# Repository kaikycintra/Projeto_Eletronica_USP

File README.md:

# SSC0180 - Eletrônica para Computação

Repositório para os trabalhos desenvolvidos na disciplina SSC0180 - Eletrônica para Computação, ministrada pelo professor Eduardo do Valle Simoes da USP

Membros dos projetos:

- Antônio Carlos de Almeida Micheli Neto - 14559013
- Maria Rita Gomides Cruz Hott - 14758717
- Kaiky Henrique Ribeiro Cintra - 13731160
- Luiz Fellipe Catuzzi Araujo Hotoshi - 11871198
- Julia Cavallio Orlando - 14758721

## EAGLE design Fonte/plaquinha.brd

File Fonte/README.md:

# Fonte
Nesse projeto, montamos uma fonte de tensão ajustável de 3V a 12V com capacidade de 100mA partindo de uma corrente alternada de 127V e 60Hz.

&nbsp;

Nós e a fonte <3

## Vídeos
Fonte construída: https://youtu.be/3VAhmxHJs3s

Functionamento do circuito: https://youtu.be/wee167FJJZs

## Componentes do Circuito

| Componente | Preço |
| --- | --- |
| Capacitor 1mF x2 | R$0,50 * 2 = R$1,00 |
| LED x2 | R$0,50 * 2 = R$1,00 |
| Diodo Zener 13V x2 | R$0,62 * 2 = R$1,24 |
| Transistor NPN 60V | R$1,60 |
| Potenciômetro Linear 10kΩ | R$7,00 |
| Resistor 3k3Ω x10 | R$0,07 * 10 = R$0,70 |
| Resistor 4k7Ω x10 | R$0,07 * 10 = R$0,70 |
| Fusível 1,5A | R$1,10 |
| Protoboard BB-01 | R$20,40 |
| Jumper macho-macho 20cm x10 | R$0,70 * 10 = R$7,00 |
| Plug AC 10A | R$6,00 |
| ***TOTAL*** | ***R$47,74*** |

No circuito real nós utilizamos um capacitor de 560μF porque nos venderam o modelo errado. O circuito funcionou como previsto.
Também realizamos a troca de um dos resistores para uma resistência menor já que as conexões reais estavam apresentando valores diferentes.
*Componentes comprados na Ca&Ma em São Carlos, 21/06/2023

### Transformador: 
Dispositivo elétrico que consegue alterar a tensão elétrica de entrada para níveis mais apropriados para uma aplicação específica, fazendo uso de enrolamentos e princípios eletromagnéticos da Lei de Faraday-Lenz. Neste projeto, utilizamos um transformador do laboratório que pôde ajustar a tensão em uma razão de 7.3 entre saída e entrada.
### Diodos:
Componentes elétricos que permitem o fluxo de corrente elétrica em uma única direção. No projeto, são utilizados para montar uma ponte de diodos, que atua como um retificador de tensão, aproveitando ambos os ciclos da corrente alternada.
### Resistores:
Componentes com resistência fixa que garantem o ajuste da corrente elétrica no circuito, permitindo não queimar nada outras partes essenciais.
### Capacitor:
Dispositivo elétrico que consegue armazenar pequenas quantidades de carga elétrica, fornecendo corrente contínua se a tensão interna for maior que a externa. Para conseguir uma flutuação (ripple) menor que 10%, seria necessário um capacitor de no mínimo 790μF (conforme mostrado na seção de cálculos abaixo). No entanto, utilizamos um de 1mF por apresentar vantagens e estar mais barato.
### Potenciômetro:
Componente com resistência ajustável que permite regular o fluxo de corrente e, consequentemente, alterar os níveis de tensão do circuito. Neste projeto, foi empregado para possibilitar a escolha dos níveis de tensão entre 3V a 12V, conforme especificado.
### Diodo Zener:
Uma variação do diodo comum, que só permite o fluxo de corrente elétrica se a tensão aplicada for superior à tensão de trabalho especificada pelo fabricante. Isso limita a voltagem máxima permitida pelo circuito. No projeto, foi usado para garantir que a tensão ficasse abaixo de 13V no final do circuito.
### Transistor:
Componente elétrico que pode alterar ou amplificar sinais e potência elétrica. No projeto, foi empregado para ajustar a corrente elétrica no final do circuito.

## Funcionamento:
### Transformação:
Nesta fase, os sinais elétricos de entrada (corrente alternada com tensão de 127V e frequência de 60Hz) têm sua diferença de potencial diminuída pelo transformador para níveis próximos a 24,6V, mantendo o resto das características da onda.
### Retificação:
Nesta fase, os sinais elétricos em corrente alternada (vindos da fase de transformação) são retificados para um sinal continuamente positivo pela ação da ponte de diodos. A disposição dos diodos no circuito permite ou bloqueia a passagem de corrente elétrica, definindo um sentido único para o fluxo de elétrons durante ambos os ciclos da onda. O resultado é uma reflexão completa dos valores negativos de tensão em relação ao eixo do gráfico.
### Filtragem: 
Nesta fase, o capacitor libera corrente elétrica nos momentos de diminuição na voltagem de entrada, tornando a saída de tensão quase contínua. As imperfeições são caracterizadas pelo ripple.
### Regulação:
Nesta fase, o diodo Zener corrige o ripple ao limitar a voltagem da curva em 13V. Assim, a saída do sistema apresenta uma tensão fixa e constante com pequenas imperfeições. Finalmente, o potenciômetro é acionado para regular o valor de saída entre os especificados 3V e 12V.

## Cálculos
### Etapa do transformador:
Primeiro, calculamos a tensão de pico (que representa o ápice da curva senoidal da tensão):

Vpico = Ventrada * √2

Vpico = tensão de pico

Ventrada = tensão de entrada da tomada (127V)

Vpico = 127 * √2 = 180V

Como queremos um transformador com uma razão de 1/7,3, a tensão de saída (Vs) será:

1/7,3 = Vs/180

Vs = 24,6V

Como o zener precisa de uma tensão mínima de 0,7V cada, devemos subtrair 1,4V da tensão de saída:

Vs = 24,6V - 1,4V

Vs = 23,2V

### Ripple:
Consideramos uma tensão de ripple de 10% da tensão de saída, logo:

Vripple = 0,1 * 23,2

Vripple = 2,32V

### Tensão média:
Como a corrente é alternada, os valores da ddp (diferença de potencial) e da corrente elétrica se alternam entre máximos e mínimos. 

Para obter resultados aproximados do circuito, calculamos a tensão média.

Vmin = 23,2V - 2,32V = 20,8V

Vmed = (Vmáx + Vmin)/2

Vmed = (23,2V + 20,8V)/2

Vmed = 22V

### Correntes:
Calculamos as correntes nos diferentes componentes do circuito:

&nbsp;

iLed:

iLed = Vmed/Rled

iLed = 22V/3300Ω

iLed = 6,6mA

Vmed = tensão média

Rled = resistência no LED (compramos a resistência e a conectamos em série com o LED)

&nbsp;

iZener:

iZener = (Vmed - Vz)/R

iZener = (22V - 13V)/3300Ω

iZener = 2,7mA

Vmed = tensão média

Vz = tensão do zener (compramos um diodo de 13V)

R = resistência (compramos a resistência e a conectamos com o diodo de zener)

&nbsp;

iPotenciômetro:

iPotenciômetro = Vmed/(Rp + R + Rz)

iPotenciômetro = 22V/(10000Ω + 4700Ω + 3300Ω)

iPotenciômetro = 1,2mA

Vmed = tensão média

Rp = resistência do potenciômetro

R = resistência (compramos a resistência e a colocamos em série com o potenciômetro)

Rz = resistência do diodo de zener

&nbsp;

iSaída:

iSaída = 100mA (saída esperada na fonte)

### Capacitância:
Para calcular a capacitância correta para filtrar o sistema, utilizamos a seguinte fórmula:

C = iF * Vripple

C = 110mA * 2 * 60Hz * 2,32V

C ≈ 790μF

## O circuito

[Circuito no Falstad](https://tinyurl.com/2mrqdjvw)

Esquemático no EAGLE

Board no EAGLE

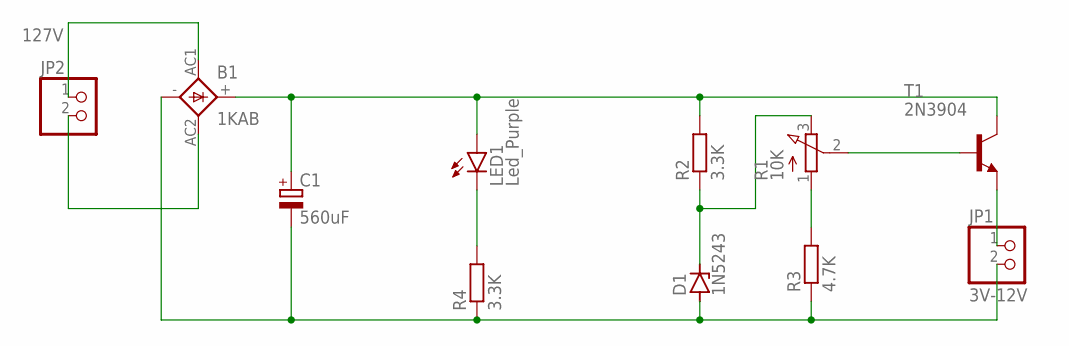
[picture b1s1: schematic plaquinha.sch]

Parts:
B1: 1KAB
C1: 560uF; E5-10,5
D1: 1N5243; DO41Z10
JP1: 3V-12V; 1X02
JP2: 127V; 1X02
LED1: Led_Purple; LED5MM
R1: 10K; 3RP/1610N
R2, R4: 3.3K; 0204/7
R3: 4.7K; 0204/7
T1: 2N3904; TO92

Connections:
unnamed: D1.C, R1.3 (E), R2.1
unnamed: JP1.1, T1.3 (E)
unnamed: LED1.K (C), R4.2
unnamed: B1.+, C1.+, LED1.A, R2.2, T1.1 (C)
unnamed: B1.AC1, JP2.1
unnamed: R1.1 (A), R3.2
unnamed: B1.AC2, JP2.2
unnamed: R1.2 (S), T1.2 (B)
unnamed: B1.-, C1.-, D1.A, JP1.2, R3.1, R4.1

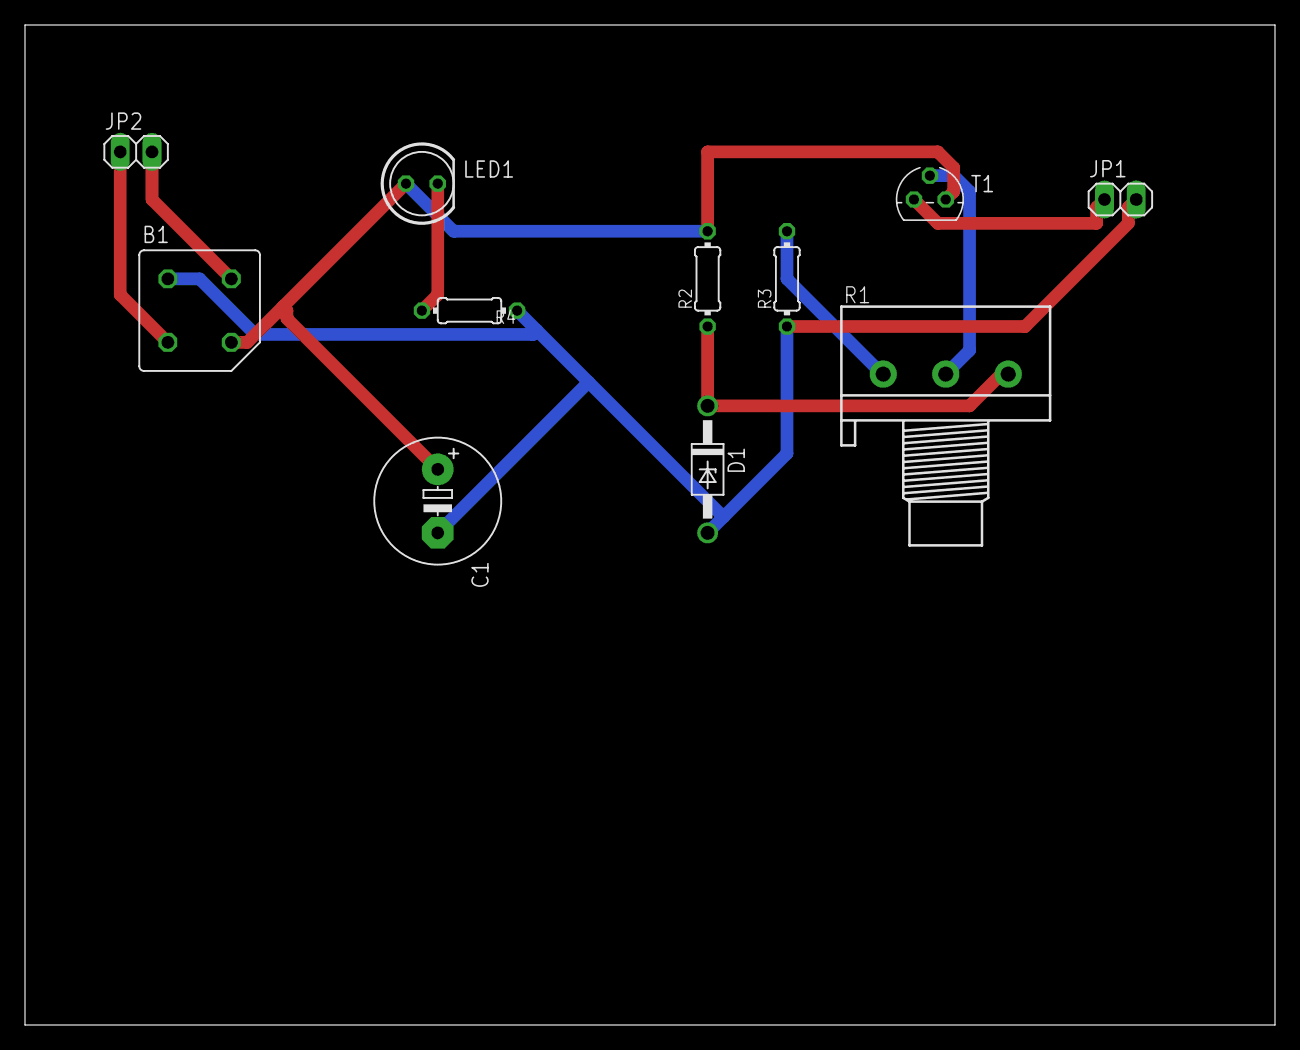
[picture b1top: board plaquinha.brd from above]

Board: 2 copper layers, 100.0 x 80.0 mm, 11 parts (0 on the bottom side), 9 nets.

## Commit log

2023-06-20 Create Snake file to add second project
2023-06-20 Create Snake directory
2023-07-13 removed some files
2023-07-13 renamed some files
